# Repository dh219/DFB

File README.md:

## David's Falcon Booster (DFB)

#### An attempt to build a low-cost memory expansion and accelerator board for the Atari Falcon.

The primary goals of the project are to:

* Be a plug-in board requiring no soldering on the Falcon;
* Increase available RAM beyond the 14MB the stock Falcon can be expanded to;
* Be low cost;
* Provide some acceleration;
* Allow the PSU to remain in the case;
* Be open source.

Some development narration on this project is provided in the [Wiki](https://github.com/dh219/DFB/wiki).

Firmware source (ISE), board design files (KiCAD) and any source for support programs are published at each release.

#### Capabilities

As of 2024 the published firmware supports 64 (2x32) or 128 (2x64) MB of TT-RAM.

It supports only a PGA128 MC68030. The board has been tested between 32 and 50MHz with the CPU normally being the limiting factor.

The FPU is optional and can be run at half the CPU speed, or with an independent oscillator. This is configured by a resistor placement choice.

The Falcon's on-board FPU, if fitted, should be removed to prevent bus conflicts.

---

*Copyright 2020-24 D Henderson, released under GPL2.0*

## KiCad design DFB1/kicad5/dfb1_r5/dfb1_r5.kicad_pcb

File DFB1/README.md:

## David's Falcon Booster Mark 1 (DFB1)

#### Hardware

The directory *kicad5* contains all the Kicad 5 project files and libraries necessary to order or edit the DFB1 PCB.

Kicad is an open source EDA suite. https://www.kicad.org/

Premade gerber files may be found in the releases.

#### Firmware

##### Building

The directory *ise* contains the project files, verilog source and hardware definition files needed to build the firmware for the CPLD.

AMD/Xilinx's ISE Design Suite is required to edit and synthesise the CPLD firmware. Tested with ISE Webpack v14.7.

https://www.xilinx.com/products/design-tools/ise-design-suite/ise-webpack.html

Precompiled (JEDEC) firmwares may be found in the releases.

##### Flashing

Flashing the CPLD can be achieved with the free and open source xc3sprog tool and a Xilinx programmer, or a Raspberry Pi.

http://xc3sprog.sourceforge.net/

https://linuxjedi.co.uk/2021/11/25/revisiting-xilinx-jtag-programming-from-a-raspberry-pi/

#### Assembling

Pick and place positioning files and automated bill of materials file are not yet available, but when they are the board house may be able to partially assemble boards for you.

In the meantime, and for hobbiests, a hand assembly video guide is available on my YouTube channel:

https://www.youtube.com/playlist?list=PLZBirr2xVnY4OkgEWdXNjq90gBGzXah9X

#### Software

I recommend Anders Granlund's TFTools suite to enable the TT-RAM on the DFB1 board. FASTRAM.PRG detects and activates the TT-RAM. MAPROM.PRG will additionally copy TOS to TT-RAM for even better performance but may require a cold boot to work completely correctly. BLITFIX.PRG does not, unfortunately, work with the Falcon.

https://github.com/agranlund/tftools

NVDI is recommended to use the stock TOS4 desktop with TT-RAM enabled as there is no way of disabling the Blitter in TOS4 and unfortunately the Blitter is not compatible with TT-RAM. NVDI replaces the VDI calls that use the Blitter.

An excellent alternative to all the above is EmuTOS, but sadly, as of version 1.1.1, it does not support the Falcon's 16-bit true colour mode.

https://emutos.sourceforge.io/

---

*Copyright 2020-21 D Henderson, released under GPL2.0*

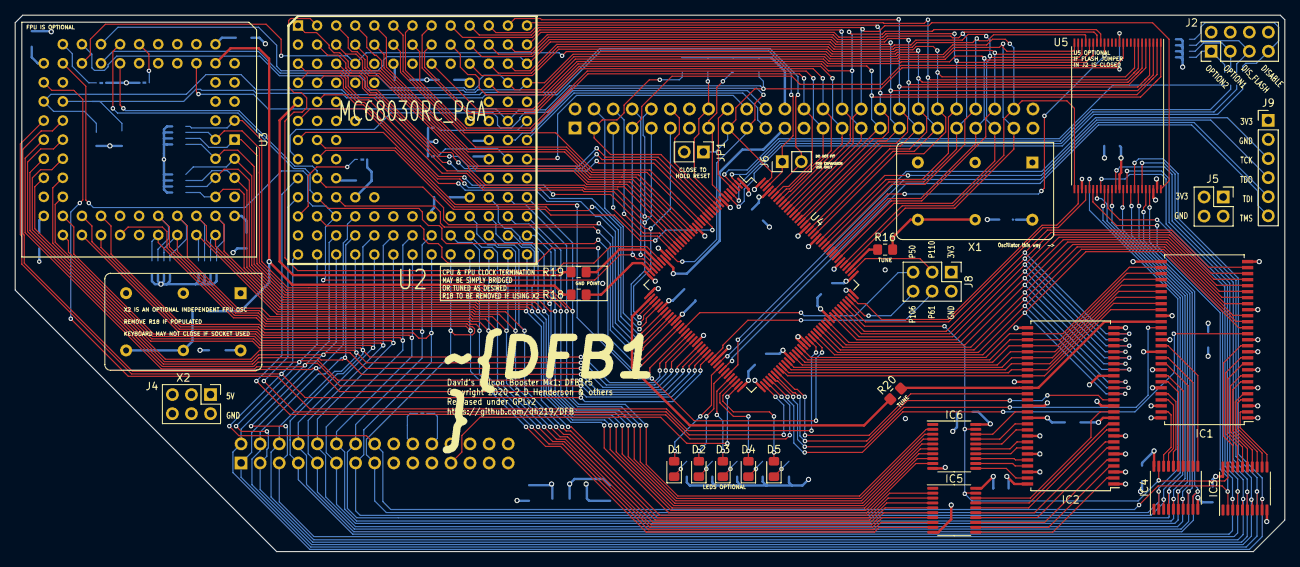
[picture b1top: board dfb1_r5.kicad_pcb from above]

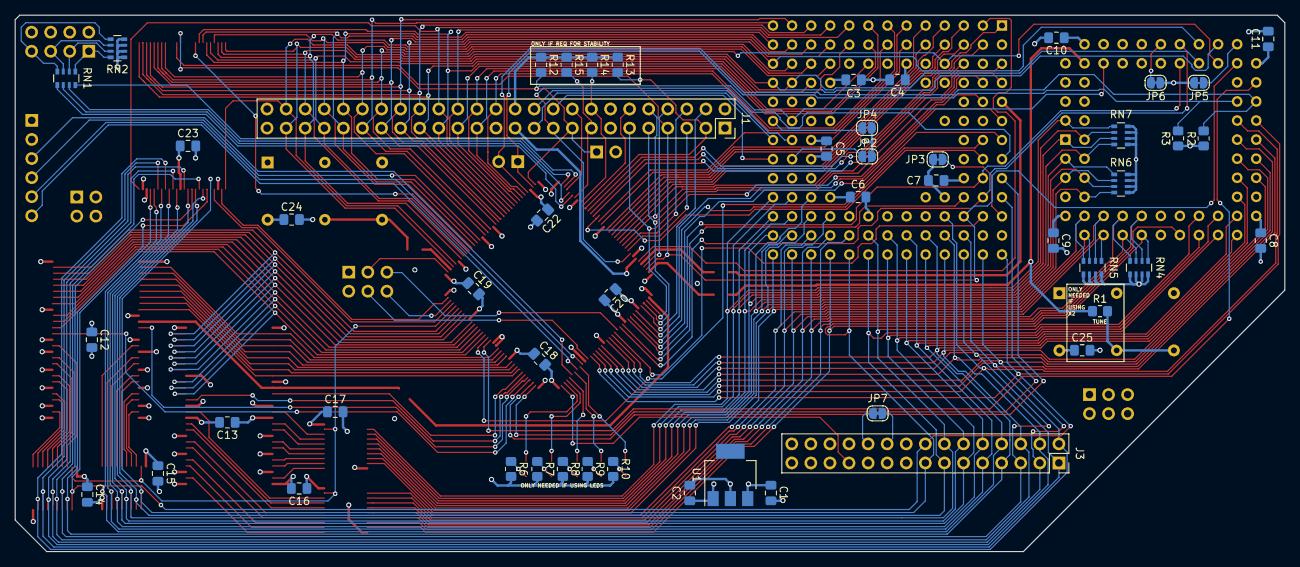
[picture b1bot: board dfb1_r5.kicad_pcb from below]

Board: 4 copper layers, 169.0 x 71.4 mm, 79 parts (51 on the bottom side), 204 nets.

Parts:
C1, C3, C10, C19, C22: 10u; C_0805_2012Metric_Pad1.18x1.45mm_HandSolder
C2, C4, C6, C7, C8, C9, C11, C12, C13, C14, C15, C16, C17, C18, C20, C23, C24, C25: 100n; C_0805_2012Metric_Pad1.18x1.45mm_HandSolder
C5: 330p; C_0805_2012Metric_Pad1.18x1.45mm_HandSolder
D1, D2, D3, D4, D5: LED; LED_0805_2012Metric_Pad1.15x1.40mm_HandSolder
IC1, IC2: IS42S16320D-7TL; TSOP-II-54_22.2x10.16mm_P0.8mm
IC3, IC4, IC5, IC6: SN74CB3T3245PW; TSSOP-20_4.4x6.5mm_P0.65mm
J1: Conn_01x50; PinSocket_2x25_P2.54mm_Vertical
J2: Conn_02x04_Odd_Even; PinHeader_2x04_P2.54mm_Vertical
J3: Conn_01x30; PinSocket_2x15_P2.54mm_Vertical
J4, J8: Conn_02x03_Odd_Even; PinHeader_2x03_P2.54mm_Vertical
J5: Conn_02x02_Odd_Even; PinHeader_2x02_P2.54mm_Vertical
J6: Conn_01x02_Female; PinHeader_1x02_P2.54mm_Vertical
J9: Conn_01x06_Male; PinHeader_1x06_P2.54mm_Vertical
JP1: Jumper_NO_Small; PinHeader_1x02_P2.54mm_Vertical
JP2, JP3, JP4, JP5, JP6, JP7: Jumper_NC_Small; SolderJumper-2_P1.3mm_Bridged_RoundedPad1.0x1.5mm_DAVID
R1, R16, R18, R19, R20: 33R NOMINAL; R_0805_2012Metric_Pad1.20x1.40mm_HandSolder
R2, R3: 2k2; R_0805_2012Metric_Pad1.20x1.40mm_HandSolder
R6, R7, R8, R9, R10: 1k; R_0805_2012Metric_Pad1.20x1.40mm_HandSolder
R12: 4k7 OPTION; R_0805_2012Metric_Pad1.20x1.40mm_HandSolder
R13, R14, R15: 10k OPTION; R_0805_2012Metric_Pad1.20x1.40mm_HandSolder
RN1, RN2, RN4, RN5, RN6, RN7: 10K; R_Array_Convex_4x0603
U1: LM1117-3.3; SOT-223
U2: MC68030RC_PGA
U3: MC68882; PLCC-68_THT-Socket
U4: XC95288XL-10TQG144I; TQFP-144_20x20mm_P0.5mm
U5: 29F800C-TSOP-48; TSOP-I-48_18.4x12mm_P0.5mm
X1, X2: CXO_DIP14_DIP8_DUAL; Oscillator_DIP-14-DUAL

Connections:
/68030/CDIS: JP2.1, U2.H12
/68030/CIIN: JP3.1, U2.L1
/68030/FPUSIZE: JP6.1, U3.18
/68030/FPU_A0: JP5.1, U3.26
/68030/MMUDIS: JP4.1, U2.F13
/CPLD/LED1: D1.2, U4.64
/CPLD/LED2: D2.2, U4.66
/CPLD/LED3: D3.2, U4.68
/CPLD/LED4: D4.2, U4.69
/CPLD/LED5: D5.2, U4.70
/CPLD/P50: J8.5, U4.50
/CPLD/P61: J8.4, U4.61
/CPLD/P106: J8.6, U4.106
/CPLD/P110: J8.3, U4.110
/CPLD/TCK: J9.3, U4.67
/CPLD/TDI: J9.5, U4.63
/CPLD/TDO: J9.4, U4.122
/CPLD/TMS: J9.6, U4.65
/CPUBGI: J3.22, JP7.2
/CPUBGO: J3.20, JP7.1
/ENABLE_J: J2.7, RN1.4, RN2.5
/EN_ALTRAM_J: J2.3, RN1.2, RN2.7
/EN_FLASH_J: J2.5, RN1.3, RN2.6
/OPTION_J: J2.1, RN1.1, RN2.8
A0: U2.A2, U4.31
A1: J1.48, U2.C4, U3.25, U4.113, U5.25
A2: J1.47, U2.D13, U3.24, U4.112, U5.24
A3: J1.46, U2.D12, U3.23, U4.116, U5.23
A4: J1.45, U2.C13, U3.22, U4.115, U5.22
A5: J1.44, U2.C12, U4.119, U5.21
A6: J1.43, U2.D11, U4.117, U5.20
A7: J1.42, U2.B13, U4.121, U5.19
A8: J1.41, U2.B12, U4.120, U5.18
A9: J1.40, U2.C11, U4.124, U5.8
A10: J1.39, U2.A13, U4.125, U5.7
A11: J1.38, U2.C10, U4.126, U5.6
A12: J1.37, U2.B11, U4.128, U5.5
A13: J1.36, U2.A12, U4.129, U5.4
A14: J1.35, U2.B10, U4.130, U5.3
A15: J1.34, U2.A11, U4.131, U5.2
A16: J1.33, U2.B9, U4.132, U5.1
A17: J1.32, U2.A10, U4.134, U5.48
A18: J1.31, U2.C8, U4.133, U5.17
A19: J1.30, U2.A9, U4.135
A20: J1.29, U2.B8, U4.136
A21: J1.28, U2.A8, U4.137
A22: J1.27, U2.B7, U4.138
A23: J1.26, U2.A7, U4.139
A24: U2.A6, U4.16
A25: U2.B6, U4.17
A26: U2.A5, U4.19
A27: U2.B5, U4.20
A28: U2.A4, U4.21
A29: U2.B4, U4.22
A30: U2.A3, U4.23
A31: U2.B3, U4.24
BA0: IC1.20, IC2.20, U4.96
BA1: IC1.21, IC2.21, U4.97
BMODE: J1.12, U4.10
CLKOSC: R16.1, U4.111
CPUCLK: R19.2, U2.E1
D0: IC6.2, RN7.1, U2.K13, U3.3
D1: IC6.3, RN7.2, U2.K12, U3.2
D2: IC6.4, RN7.3, U2.L13, U3.1
D3: IC6.6, RN7.4, U2.M13, U3.68
D4: IC6.5, RN6.1, U2.L12, U3.67
D5: IC6.7, RN6.3, U2.K11, U3.66
D6: IC6.8, RN6.2, U2.M12, U3.65
D7: IC6.9, RN6.4, U2.L11, U3.64
D8: IC5.2, RN5.4, U2.N13, U3.62
D9: IC5.3, RN5.3, U2.M11, U3.60
D10: IC5.4, RN5.2, U2.L10, U3.59
D11: IC5.5, RN5.1, U2.N12, U3.58
D12: IC5.6, RN4.4, U2.M10, U3.57
D13: IC5.7, RN4.3, U2.N11, U3.56
D14: IC5.8, RN4.2, U2.M9, U3.55
D15: IC5.9, RN4.1, U2.N10, U3.54
D16: IC4.2, J3.15, U2.N9, U3.50, U5.29
D17: IC4.4, J3.14, U2.M8, U3.49, U5.31
D18: IC4.3, J3.13, U2.N8, U3.48, U5.33
D19: IC4.5, J3.12, U2.N7, U3.47, U5.35
D20: IC4.6, J3.11, U2.M7, U3.46, U5.38
D21: IC4.7, J3.10, U2.N6, U3.45, U5.40
D22: IC4.8, J3.9, U2.M6, U3.44, U5.42
D23: IC4.9, J3.8, U2.N5, U3.42, U5.44
D24: IC3.3, J3.7, U2.M5, U3.40, U4.52, U5.30
D25: IC3.5, J3.6, U2.N4, U3.39, U4.53, U5.32
D26: IC3.4, J3.5, U2.N3, U3.38, U4.54, U5.34
D27: IC3.7, J3.4, U2.M4, U3.37, U4.56, U5.36
D28: IC3.6, J3.3, U2.N2, U3.36, U4.57, U5.39
D29: IC3.9, J3.2, U2.M3, U3.35, U4.58, U5.41
D30: IC3.8, J3.1, U2.L4, U3.34, U4.59, U5.43
D31: IC3.2, J3.16, U2.N1, U3.33, U4.60, U5.45
DQM0: IC1.15, U4.76
DQM1: IC1.39, U4.77
DQM2: IC2.15, U4.78
DQM3: IC2.39, U4.79
ENABLE: RN1.5, U4.6
EN_ALTRAM: RN1.7, U4.2
EN_FLASH: RN1.6, U4.5
FC0: J1.11, U2.D2, U4.39
FC1: J1.10, U2.C1, U4.25
FC2: J1.9, U2.D1, U4.40
FPUCLK: R1.1, R18.2, U3.11
GND: C1.2, C2.2, C3.2, C4.2, C5.2, C6.2, C7.2, C8.2, C9.2, C10.2, C11.2, C12.2, C13.2, C14.2, C15.2, C16.2, C17.2, C18.2, C19.2, C20.2, C22.2, C23.2, C24.2, C25.2, IC1.6, IC1.12, IC1.19, IC1.28, IC1.41, IC1.46, IC1.52, IC1.54, IC2.6, IC2.12, IC2.19, IC2.28, IC2.41, IC2.46, IC2.52, IC2.54, IC3.10, IC4.10, IC5.10, IC6.10, J1.1, J1.2, J2.2, J2.4, J2.6, J2.8, J3.17, J3.18, J3.19, J4.2, J4.4, J4.6, J5.2, J5.4, J8.2, J9.2, JP1.2, R6.2, R7.2, R8.2, R9.2, R10.2, U1.1, U2.C5, U2.C7, U2.C9, U2.E3, U2.E11, U2.F3, U2.G3, U2.G11, U2.J3, U2.J11, U2.L5, U2.L7, U2.L8, U2.L9, U3.5, U3.6, U3.7, U3.8, U3.9, U3.12, U3.14, U3.19, U3.30, U3.41, U3.51, U3.63, U4.18, U4.29, U4.36, U4.47, U4.62, U4.72, U4.89, U4.90, U4.99, U4.108, U4.114, U4.123, U4.144, U5.27, U5.46, X1.4, X1.7, X2.4, X2.7
KHZ500: J3.23, U4.71
MA0: IC1.23, IC2.23, U4.100
MA1: IC1.24, IC2.24, U4.101
MA2: IC1.25, IC2.25, U4.102
MA3: IC1.26, IC2.26, U4.103
MA4: IC1.29, IC2.29, U4.88
MA5: IC1.30, IC2.30, U4.87
MA6: IC1.31, IC2.31, U4.86
MA7: IC1.32, IC2.32, U4.85
MA8: IC1.33, IC2.33, U4.83
MA9: IC1.34, IC2.34, U4.82
MA10: IC1.22, IC2.22, U4.98
MA11: IC1.35, IC2.35, U4.81
MA12: IC1.36, IC2.36, U4.80
MD0: IC2.2, IC5.11
MD1: IC2.4, IC5.12
MD2: IC2.5, IC5.13
MD3: IC2.7, IC5.14
MD4: IC2.8, IC5.15
MD5: IC2.10, IC5.16
MD6: IC2.11, IC5.17
MD7: IC2.13, IC5.18
MD8: IC2.42, IC6.18
MD9: IC2.44, IC6.17
MD10: IC2.45, IC6.16
MD11: IC2.47, IC6.15
MD12: IC2.48, IC6.14
MD13: IC2.50, IC6.13
MD14: IC2.51, IC6.12
MD15: IC2.53, IC6.11
MD16: IC1.2, IC3.11
MD17: IC1.4, IC3.12
MD18: IC1.5, IC3.13
MD19: IC1.7, IC3.14
MD20: IC1.8, IC3.15
MD21: IC1.10, IC3.16
MD22: IC1.11, IC3.17
MD23: IC1.13, IC3.18
MD24: IC1.42, IC4.11
MD25: IC1.44, IC4.12
MD26: IC1.45, IC4.13
MD27: IC1.47, IC4.14
MD28: IC1.48, IC4.15
MD29: IC1.50, IC4.16
MD30: IC1.51, IC4.17
MD31: IC1.53, IC4.18
unnamed: D1.1, R10.1
unnamed: D2.1, R9.1
unnamed: D3.1, R8.1
unnamed: D4.1, R7.1
unnamed: D5.1, R6.1
unnamed: R1.2, X2.8, X2.11
unnamed: R16.2, X1.8, X1.11
unnamed: R18.1, U4.35
unnamed: R19.1, U4.32
unnamed: R20.1, U4.38
OPTION: RN1.8, U4.3
RAMCLK: IC1.38, IC2.38, R20.2
ROM_A19: U4.118, U5.16
SIZ0: U2.L2, U4.51
SIZ1: U2.K3, U4.48
VCC: C1.1, C3.1, C4.1, C5.1, C6.1, C7.1, C8.1, C9.1, C10.1, C11.1, C23.1, C24.1, C25.1, J1.24, J1.25, J3.28, J3.29, J3.30, J4.1, J4.3, J4.5, JP2.2, JP3.2, JP4.2, JP5.2, JP6.2, R2.1, R3.1, R12.1, R13.1, R14.1, R15.1, RN4.5, RN4.6, RN4.7, RN4.8, RN5.5, RN5.6, RN5.7, RN5.8, RN6.5, RN6.6, RN6.7, RN6.8, RN7.5, RN7.6, RN7.7, RN7.8, U1.3, U2.C6, U2.D4, U2.D10, U2.F2, U2.F11, U2.H3, U2.H11, U2.K4, U2.K10, U2.L6, U3.10, U3.16, U3.17, U3.27, U3.43, U3.52, U3.53, U3.61, U5.37, U5.47, X1.14, X2.14
VCC3: C2.1, C12.1, C13.1, C14.1, C15.1, C16.1, C17.1, C18.1, C19.1, C20.1, C22.1, IC1.1, IC1.3, IC1.9, IC1.14, IC1.27, IC1.37, IC1.43, IC1.49, IC2.1, IC2.3, IC2.9, IC2.14, IC2.27, IC2.37, IC2.43, IC2.49, IC3.20, IC4.20, IC5.20, IC6.20, J5.1, J5.3, J8.1, J9.1, RN2.1, RN2.2, RN2.3, RN2.4, U1.2, U4.1, U4.8, U4.37, U4.42, U4.55, U4.73, U4.84, U4.109, U4.127, U4.141
XCPUCLK: J1.23, U4.30
XR~W: J1.7, U2.L3, U3.28, U4.34, U5.11
~AS: U2.J2, U3.21, U4.46
~AVEC: U2.E2, U4.43
~BERR: J1.19, U2.H1, U4.28
~BG: U2.B2, U4.12
~BGK: U2.C3, U4.14
~BOE: IC3.19, IC4.19, IC5.19, IC6.19, U4.104
~BR: U2.A1, U4.13
~CAS: IC1.17, IC2.17, U4.94
~CBACK: U2.J1, U4.75
~CBREQ: U2.K1, U4.74
~DS: U2.K2, U3.20, U4.49
~DSACK0: U2.F1, U4.45
~DSACK1: U2.G2, U4.44
~FPUCS: U3.29, U4.91
~FPUDSACK0: J6.2, R2.2, U3.31, U4.140
~FPUDSACK1: J6.1, R3.2, U3.32, U4.142
~HLT: U2.H2, U4.15
~IPL0: J1.20, U2.H13
~IPL1: J1.21, U2.G13
~IPL2: J1.22, U2.G12
~LDS: J1.5, U4.27
~RAMWE: IC1.16, IC2.16, U4.93
~RAS: IC1.18, IC2.18, U4.95
~ROMCE: U4.107, U5.26
~ROMOE: U4.105, U5.28
~RST: J1.17, JP1.1, R12.2, U2.F12, U3.13, U4.143, U5.12
~STERM: U2.G1, U4.92
~UDS: J1.6, U4.26
~XAS: J1.4, U4.41
~XBG: J1.15, R15.2, U4.7
~XBGK: J1.3, R13.2, U4.11
~XBR: J1.16, R14.2, U4.9
~XDTACK: J1.8, U4.33
~XHALT: J1.18, U4.4

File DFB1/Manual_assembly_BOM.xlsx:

Assembly Order | Designator | Package | Quantity | Designation | Mouser part | Farnell part | LCSC part | RS part | Approx indiv cost (GBP ex VAT) | Approx line cost | Approximate overall component cost (GBP)
1 | U4 | TQFP-144_20x20mm_P0.5mm | 1 | XC95288XL-10TQG144I |  | 2907289 |  |  | 22 | 22 | NO VAT
1 | C25,C24,C11,C9,C8,C23,C17,C16,C15,C14,C13,C12,C20,C18,C2,C7,C6,C4 | C_0805_2012Metric_Pad1.18x1.45mm_HandSolder | 18 | 100n | Jellybean |  |  |  | 0.03 | 0.54 | 63.04
1 | C22,C10,C19,C1,C3 | C_0805_2012Metric_Pad1.18x1.45mm_HandSolder | 5 | 10u | Jellybean |  |  |  | 0.03 | 0.15
1 | C5 | C_0805_2012Metric_Pad1.18x1.45mm_HandSolder | 1 | 330p | Jellybean |  |  |  | 0.03 | 0.03 | +VAT
1 | R3,R2 | R_0805_2012Metric_Pad1.20x1.40mm_HandSolder | 2 | 2k2 | Jellybean |  |  |  | 0.03 | 0.06 | 75.648
1 | R18,R1,R20,R19,R16 | R_0805_2012Metric_Pad1.20x1.40mm_HandSolder | 5 | 33R NOMINAL | Jellybean |  |  |  | 0.03 | 0.15
1 | RN7,RN6,RN5,RN4,RN2,RN1 | R_Array_Convex_4x0603 | 6 | 10K 1206 |  | 3550050 |  |  | 0.04 | 0.24
1 | R12 | R_0805_2012Metric_Pad1.20x1.40mm_HandSolder | 1 | 4k7 OPTION | Jellybean |  |  |  | 0.03 | 0.03
1 | U1 | SOT-223 | 1 | LM1117-3.3 |  | 3588827 |  |  | 0.65 | 0.65
1 | J9 | PinHeader_1x06_P2.54mm_Vertical | 1 | Conn_01x06_Male | Jellybean |  |  |  | 0.06 | 0.06
TEST JTAG AND PROGRAM |  |  |  |  |  |  |  |  |  | 0
 |  |  |  |  |  |  |  |  |  | 0
2 | X1 | Oscillator_DIP-14-DUAL | 1 | 5V DIP 8 or DIP14 |  | 2508732 |  |  | 3.1 | 3.1
2 | J3 | PinSocket_2x15_P2.54mm_Vertical | 1 | Conn_01x30 |  | 2847247 |  |  | 0.81 | 0.81
2 | J1 | PinSocket_2x25_P2.54mm_Vertical | 1 | Conn_01x50 |  | 2847249 |  |  | 1.35 | 1.35
2 | U2 | MC68030RC_PGA | 1 | MC68030RC_PGA | See Exxos store |  |  |  | 8 | 8
2 | J2 | PinHeader_2x04_P2.54mm_Vertical | 1 | Conn_02x04_Odd_Even | Jellybean |  |  |  | 0.08 | 0.08
TEST IN FALCON SHOULD NOW ACCELERATE |  |  |  |  |  |  |  |  |  | 0
 |  |  |  |  |  |  |  |  |  | 0
3 | IC6,IC5,IC4,IC3 | TSSOP-20_4.4x6.5mm_P0.65mm | 4 | SN74CB3T3245PW |  | 3120942 |  |  | 2.1 | 8.4
3 | IC2,IC1 | TSOP-II-54_22.2x10.16mm_P0.8mm | 2 | IS42S16160G-7TLI |  | 2253829 |  |  | 3.9 | 7.8
TEST IN FALCON SHOULD NOW DETECT TTRAM AND PASS YAARTTT |  |  |  |  |  |  |  |  |  | 0
 |  |  |  |  |  |  |  |  |  | 0
ENTIRELY OPTIONAL TO TASTE |  |  |  |  |  |  |  |  |  | 0
4 | D5,D4,D3,D2,D1 | LED_0805_2012Metric_Pad1.15x1.40mm_HandSolder | 5 | LED SMD 0805 |  | 1581242 |  |  | 0.12 | 0.6
4 | R10,R9,R8,R7,R6 | R_0805_2012Metric_Pad1.20x1.40mm_HandSolder | 5 | 1k | Jellybean |  |  |  | 0.03 | 0.15
 |  |  |  |  |  |  |  |  |  | 0
4 | U3 | PLCC-68_THT-Socket | 1 | MC68882 |  | 1183031 |  |  | 2.15 | 2.15
 |  |  |  |  |  |  |  |  |  | 0
DEBUG/EXPANSION |  |  |  |  |  |  |  |  |  | 0
X | J6 | PinHeader_1x02_P2.54mm_Vertical | 1 | Conn_01x02_Male | Jellybean |  |  |  | 0.02 | 0.02
X | JP1 | PinHeader_1x02_P2.54mm_Vertical | 1 | Conn_01x02_Male | Jellybean |  |  |  | 0.02 | 0.02
X | J5 | PinHeader_2x02_P2.54mm_Vertical | 1 | Conn_02x02_Odd_Even | Jellybean |  |  |  | 0.04 | 0.04
X | J8,J4 | PinHeader_2x03_P2.54mm_Vertical | 2 | Conn_02x03_Odd_Even | Jellybean |  |  |  | 0.06 | 0.12
NOT YET TESTED |  |  |  |  |  |  |  |  |  | 0
E | U5 | TSOP-I-48_18.4x12mm_P0.5mm | 1 | 5V 29F800C-TSOP-48 |  |  |  | 914-2768 | 3.3 | 3.3
 |  |  |  |  |  |  |  |  |  | 0
ONLY FIT IF STABILITY REQUIRES (TEST EACH ONE) |  |  |  |  |  |  |  |  |  | 0
D | R15,R14,R13 | R_0805_2012Metric_Pad1.20x1.40mm_HandSolder | 3 | 10k OPTION | Jellybean |  |  |  | 0.03 | 0.09
 |  |  |  |  |  |  |  |  |  | 0
DO NOT FIT IF R18 POPULATED |  |  |  |  |  |  |  |  |  | 0
O | X2 | Oscillator_DIP-14-DUAL | 1 | 5V DIP 8 or DIP14 |  |  |  |  | 3.1 | 3.1

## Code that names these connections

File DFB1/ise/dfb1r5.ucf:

NET "A<27>" LOC = "P20" ;
NET "A<28>" LOC = "P21" ;
NET "A<29>" LOC = "P22" ;
NET "A<30>" LOC = "P23" ;
NET "A<31>" LOC = "P24" ;
NET "FC<1>" LOC = "P25" ;
NET "UDS" LOC = "P26" ;
NET "LDS" LOC = "P27" ;

NET "XBR" LOC = "P9" ;
NET "BMODE" LOC = "P10" ;
NET "XBGK" LOC = "P11" ;
NET "BG" LOC = "P12" ;
NET "BR" LOC = "P13" ;
NET "BGK" LOC = "P14" ;
NET "HLT" LOC = "P15" ;
NET "A<24>" LOC = "P16" ;
NET "A<24>" LOC = "P16" ;
NET "A<25>" LOC = "P17" ;
NET "A<26>" LOC = "P19" ;

NET "BERR" LOC = "P28" ;
NET "XCPUCLK" LOC = "P30" ;
NET "A<0>" LOC = "P31" ;
NET "CPUCLK" LOC = "P32" ;
NET "XDTACK" LOC = "P33" ;


NET "OPTION1" LOC = "P2" ;
NET "OPTION2" LOC = "P3" ;
NET "XHALT" LOC = "P4" ;
NET "EN_FLASH" LOC = "P5" ;
NET "ENABLE" LOC = "P6" ;
NET "XBG" LOC = "P7" ;


NET "XRW" LOC = "P34" ;
NET "FPUCLK" LOC = "P35" ;
NET "CLKRAM" LOC = "P38" ;
NET "FC<0>" LOC = "P39" ;
NET "FC<2>" LOC = "P40" ;
NET "XAS" LOC = "P41" ;
NET "AVEC" LOC = "P43" ;
NET "DSACK<1>" LOC = "P44" ;

NET "A<19>" LOC = "P135" ;
NET "A<20>" LOC = "P136" ;
NET "A<21>" LOC = "P137" ;
NET "A<22>" LOC = "P138" ;
NET "A<23>" LOC = "P139" ;
NET "FPUDSACK<0>" LOC = "P140" ;
NET "FPUDSACK<1>" LOC = "P142" ;
NET "RST" LOC = "P143" ;

NET "DSACK<0>" LOC = "P45" ;
NET "AS" LOC = "P46" ;
NET "SIZ<1>" LOC = "P48" ;
NET "DS" LOC = "P49" ;

NET "A<14>" LOC = "P130" ;
NET "A<15>" LOC = "P131" ;
NET "A<16>" LOC = "P132" ;
NET "A<18>" LOC = "P133" ;
NET "A<17>" LOC = "P134" ;

NET "P50" LOC = "P50" ;
NET "SIZ<0>" LOC = "P51" ;
NET "D<0>" LOC = "P52" ;
NET "D<1>" LOC = "P53" ;
NET "D<2>" LOC = "P54" ;
NET "D<3>" LOC = "P56" ;
NET "D<4>" LOC = "P57" ;
NET "D<5>" LOC = "P58" ;
NET "D<6>" LOC = "P59" ;

NET "A<6>" LOC = "P117" ;
NET "ROM_A19" LOC = "P118" ;
NET "A<5>" LOC = "P119" ;
NET "A<8>" LOC = "P120" ;
NET "A<7>" LOC = "P121" ;
NET "A<9>" LOC = "P124" ;
NET "A<10>" LOC = "P125" ;
NET "A<11>" LOC = "P126" ;
NET "A<12>" LOC = "P128" ;
NET "A<13>" LOC = "P129" ;

NET "D<7>" LOC = "P60" ;
NET "P61" LOC = "P61" ;
NET "LED<1>" LOC = "P64" ;
NET "LED<2>" LOC = "P66" ;
NET "LED<3>" LOC = "P68" ;
NET "LED<4>" LOC = "P69" ;
NET "LED<5>" LOC = "P70" ;

NET "P110" LOC = "P110" ;
NET "CLKOSC" LOC = "P111" ;
NET "A<2>" LOC = "P112" ;
NET "A<1>" LOC = "P113" ;
NET "A<4>" LOC = "P115" ;
NET "A<3>" LOC = "P116" ;

NET "KHZ500" LOC = "P71" ;
NET "CBREQ" LOC = "P74" ;
NET "CBACK" LOC = "P75" ;
NET "DQM<0>" LOC = "P76" ;
NET "DQM<1>" LOC = "P77" ;
NET "DQM<2>" LOC = "P78" ;

NET "MA<0>" LOC = "P100" ;
NET "MA<1>" LOC = "P101" ;
NET "MA<2>" LOC = "P102" ;
NET "MA<3>" LOC = "P103" ;
NET "BOE" LOC = "P104" ;
NET "ROMOE" LOC = "P105" ;
NET "P106" LOC = "P106" ;
NET "ROMCE" LOC = "P107" ;

NET "DQM<3>" LOC = "P79" ;
NET "MA<12>" LOC = "P80" ;
NET "MA<11>" LOC = "P81" ;
NET "MA<9>" LOC = "P82" ;
NET "MA<8>" LOC = "P83" ;
NET "MA<7>" LOC = "P85" ;
NET "MA<6>" LOC = "P86" ;
NET "MA<5>" LOC = "P87" ;
NET "MA<4>" LOC = "P88" ;

NET "FPUCS" LOC = "P91" ;
NET "STERM" LOC = "P92" ;
NET "RAMWE" LOC = "P93" ;
NET "CAS" LOC = "P94" ;
NET "RAS" LOC = "P95" ;
NET "BA<0>" LOC = "P96" ;
NET "BA<1>" LOC = "P97" ;
NET "MA<10>" LOC = "P98" ;
#Created by Constraints Editor (xc95288xl-tq144-10) - 2022/11/28
NET "XCPUCLK" TNM_NET = XCPUCLK;
TIMESPEC TS_XCPUCLK = PERIOD "XCPUCLK" 16 MHz HIGH 50%;
NET "KHZ500" TNM_NET = KHZ500;
TIMESPEC TS_KHZ500 = PERIOD "KHZ500" 2 us HIGH 50%;
NET "CLKOSC" TNM_NET = CLKOSC;
TIMESPEC TS_CLKOSC = PERIOD "CLKOSC" 50 MHz HIGH 50%;
#NET "CPUCLK" OFFSET = OUT 20 ns AFTER "CLKOSC";
#NET "FPUCLK" OFFSET = OUT 20 ns AFTER "CLKOSC";
#NET "CLKRAM" OFFSET = OUT 20 ns AFTER "CLKOSC";

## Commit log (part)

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2020-10-27 First readme.md
2020-10-27 Adding Falcon memory image
2020-10-27 Adding wiki_resources
2020-10-28 Adding FPU hack image
2020-10-28 Annotating image
2020-11-20 Adding some board revision snaps
2020-11-20 Reducing image size
2020-11-20 Resizeing rev1.jpeg
2020-11-20 Diag Cart first signs of life
2020-11-20 adding a screenshot of the broken cache etos boot screen
2020-11-20 added rev2b benchmark
2020-11-20 Adding rev3 kicad model
2020-12-11 Adding DSP access problem images
2020-12-11 Updating rev3 render
2020-12-12 Adding DSP schematic image
2020-12-12 Added U62
2021-05-18 Scope shots for wiki DSP page
2021-05-18 Adding FPU Hat render for rev 3
2021-05-18 A working picture of DFB1r43
2022-01-15 Initial commit of DFB1r5
2022-03-29 Uploading verilog files for ISE.
2022-03-29 Bumping copyright
2022-03-29 Adding binary firmware (JEDEC) file
2022-03-30 Adding Readme specificalyl for DFB1
2022-03-30 Correcting errant ISE version number
2022-03-31 Added a BOM for manual assembly.
2022-04-01 Corrected a part number
2022-04-07 Tweak to firmware compliation options to perhaps run a little cooler. Perhaps better for marginal (ie eBay) CPLDs. No functional changes.
2022-04-07 Correcting another out of date copyright notice.
2022-05-07 Getting flash working (albeit only 512k for now)
2022-05-07 Adding the flash-supporting JEDEC
2022-06-03 Rename dfb1r5_2200507.jed to dfb1r5_220507.jed
2022-10-18 When working on Frank's DFB1 firmware, I developed a slower but more reliable SDRAM/Flash combination. Checked in to continue work.
2022-10-18 Possible new release version -- more stable at the expense of write speed.
2022-10-31 Adding 1.0 JEDEC. Fixes flash problems. More reliable TT-RAM.
2022-10-31 Only one usable JEDEC now published
2022-11-13 Experimenting with configurable variables
2022-11-16 Added some commented out code to support direct DSACK connections in next board revision
2022-11-23 Starting work on properly published dfbflash
2022-11-24 Adding built TTP
2022-11-28 Adding some TIMESPECs
2022-12-28 Jumper labels updated to reflect production gerbers
2023-01-31 SPI work
2023-02-02 SPI work continues. Removing pointless offset instruction in the UCF
2023-02-08 SPI working with clock switch albeit in a broken way. Need to consolidate duplex mode
2023-02-08 Duplex SPI working.
2023-02-21 Extending the erase/write delay on DFBFLASH to accomodate the 1MB chips out there
2023-04-21 fixed : moved kicad custom libraries directory inside kicad project directory and added to project library tables
2023-06-23 Adding Exxos Special Limited Licence
    The Exxos store has been issued custom (non-GPL) licence to derive a commercial product from the DFB1 1.0 release.
2023-06-30 Making the erase step optional to aid 1MB flash users
2025-11-07 Experimenting with AS timing to try to speed up DSP host access. BROKEN COMMIT.
2025-11-10 Managing 100% on first test with modified GAL (no delay2). ~85% on second tests.
2026-02-11 Working on improving the bus arb state machine for a possible 1.1 firmware.
2026-02-18 Simplified the bus arb state machine one further stage
2026-06-05 Reduced the amount of xdsp_holoff to the minimum to run

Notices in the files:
DFB1/kicad5/dfb1_r5/dfb1_r5.kicad_pcb:
Copyright 2022 D Henderson
Released under the terms of the GPLv2
Copyright 2020-2 D Henderson & others
Released under GPLv2
